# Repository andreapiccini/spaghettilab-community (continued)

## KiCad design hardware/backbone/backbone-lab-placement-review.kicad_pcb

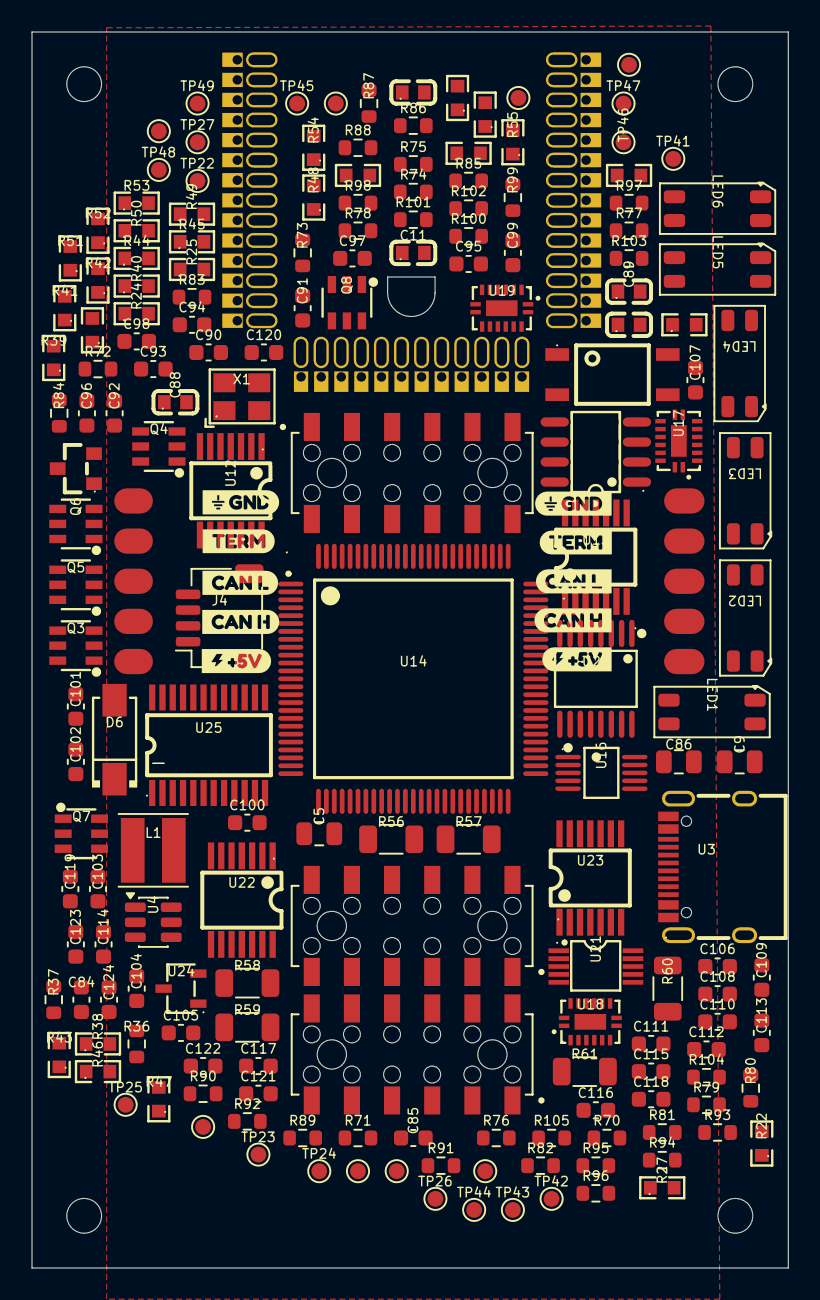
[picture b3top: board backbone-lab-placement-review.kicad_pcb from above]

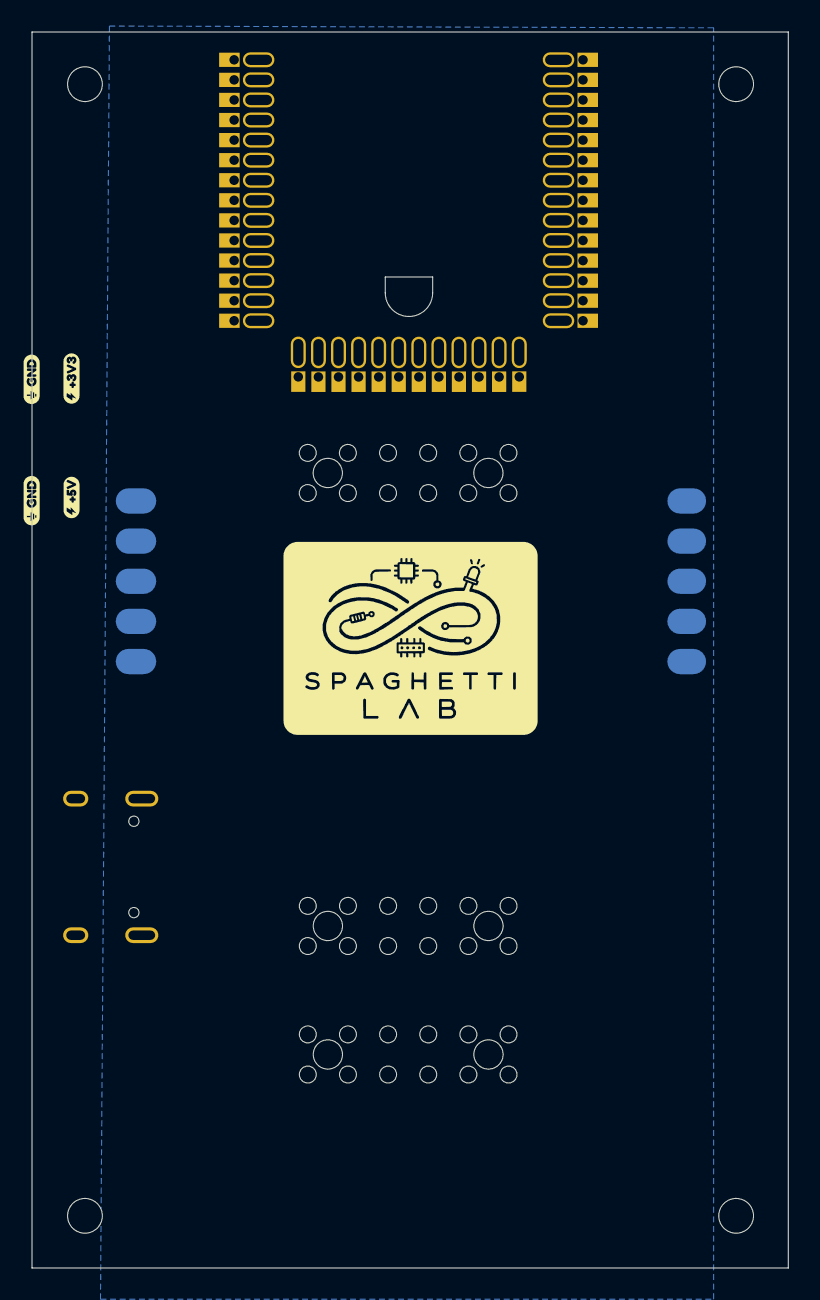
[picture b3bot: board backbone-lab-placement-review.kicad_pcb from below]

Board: 4 copper layers, 47.9 x 78.2 mm, 207 parts (13 on the bottom side), 125 nets, no tracks yet.

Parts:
C1, C74, C88, C89: 100nF; C0603
C5, C9, C86: 22uF; C_0805_2012Metric
C11: 1uF; C0603
C84, C85: 100nF/50V; C_0603_1608Metric
C90, C91, C92, C93, C94, C95, C96, C97, C98, C100, C101, C102, C105, C106, C114, C115, C116, C119, C120, C121, C122, C123, C124: 100nF; C_0603_1608Metric
C99, C103, C104, C107, C117, C118: 1uF; C_0603_1608Metric
C108, C109, C110, C111, C112, C113: 1nF; C_0603_1608Metric
D6: SS54_C22452; SMA_L4.4-W2.8-LS5.4-R-RD
H1, H2, H3, H4: MountingHole; MountingHole_2.2mm_M2_DIN965
J1, J3, J140: M20-7810645R; HARWIN_M20-7810645R
J2: FROM_PREVIOUS; Magnetic_J2_Edge_DualFace
J4: SM04B-SRSS-TB(LF)(SN); JST_SH_SM04B-SRSS-TB_1x04-1MP_P1.00mm_Horizontal
J9: TO NEXT; Magnetic_J9_Edge_DualFace
L1: 3.3uH; L_XRTC404012S
LED1, LED2, LED3, LED4, LED5, LED6: SK6812MINI-E; LED_SK6812MINI-E_FR4_Window_HandFormed
Q2: AO3401A; SOT-23_L2.9-W1.3-P1.90-LS2.4-BR
Q3, Q4, Q5, Q6, Q7, Q8: AO6604; SOT-23-6_L2.9-W1.6-P0.95-LS2.8-BL
R4: 470k; R0603
R5: 1k; R0603
R8: 120R; R0603
R15, R16: 10k; R0603
R17, R18: 33R DNP / ESP USB; R0603
R22, R27: 5.1k; R0603
R24, R25: 4.7k; R0603
R36: 33k 1%; R_0603_1608Metric
R37: 10k 1%; R_0603_1608Metric
R38, R39, R40, R41, R42, R43, R44, R45, R46, R47, R48, R49, R50, R51, R52, R53, R54, R55: 100k; R0603
R56, R57, R58, R59, R60, R61: 0.1R; R_1206_3216Metric
R70, R71, R74, R75, R76, R78, R103, R104, R105: 100k; R_0603_1608Metric
R72, R73, R83, R84: 10k; R_0603_1608Metric
R77: 4.7k 0.1% 25ppm; R_0603_1608Metric
R79, R80: 4.7k; R_0603_1608Metric
R81, R82: 22R; R_0603_1608Metric
R85, R86, R87, R88, R97: 1k; R_0603_1608Metric
R89, R90, R91, R92, R93, R94: 33R; R_0603_1608Metric
R95: 3.16k 0.1%; R_0603_1608Metric
R96: 10k 0.1%; R_0603_1608Metric
R98, R99, R100, R101, R102: 0R / ESP-only; R_0603_1608Metric
TP8, TP9, TP12, TP13, TP15, TP18, TP19, TP21: SMD/0.6mm; TestPoint_Pad_D1.0mm
TP22: AG_NRST; TestPoint_Pad_D1.0mm
TP23: AG_JTMS; TestPoint_Pad_D1.0mm
TP24: AG_JTCK; TestPoint_Pad_D1.0mm
TP25: AG_JTDI; TestPoint_Pad_D1.0mm
TP26: AG_JTDO; TestPoint_Pad_D1.0mm
TP27: AG_JNTRST; TestPoint_Pad_D1.0mm
TP41: DAC1; TestPoint_Pad_D1.0mm
TP42: ADC_SPARE_17; TestPoint_Pad_D1.0mm
TP43: ADC_SPARE_33; TestPoint_Pad_D1.0mm
TP44: ADC_SPARE_34; TestPoint_Pad_D1.0mm
TP45: ADC_SPARE_35; TestPoint_Pad_D1.0mm
TP46: ADC_SPARE_36; TestPoint_Pad_D1.0mm
TP47: AG_UART_RX; TestPoint_Pad_D1.0mm
TP48: AG_UART_TX; TestPoint_Pad_D1.0mm
TP49: AG_BOOT0; TestPoint_Pad_D1.0mm
U1: ESP32-S3-WROOM-1_1U_FlexyPin_Socket
U2: SN65HVD230DR; SOIC-8_L4.9-W3.9-P1.27-LS6.0-BL
U3: HC-TYPE-C-16P-01A; USB-C-SMD_HC-TYPE-C-16P-01A
U4: TPS562201DDCR; TSOT-23-6_Power
U8: G3VM-61VY3; SMD-4_L4.6-W3.7-P2.54-LS7.0-TL
U12, U13: SN74CBTLV3125PWR; TSSOP-14_L5.0-W4.4-P0.65-LS6.4-BL
U14: AG32VF407VGT6; LQFP-100_L14.0-W14.0-P0.50-LS16.0-TL
U16: INA226AIDGSR; MSOP-10_L3.0-W3.0-P0.50-LS5.0-BL
U17, U18, U19: 74HC4051BQ,115; DHVQFN-16_L3.5-W2.5-P0.50-BL-EP
U20: ADC128S102CIMTX/NOPB; TSSOP-16_L5.0-W4.4-P0.65-LS6.4-BL
U21: DAC60501ZDGSR; VSSOP-10_L3.0-W3.0-P0.50-LS4.9-BL
U22, U23: TLV9064IPWR; TSSOP-14_L5.0-W4.4-P0.65-LS6.4-BL
U24: REF3033AIDBZR; SOT-23-3_L3.0-W1.7-P0.95-LS2.9-BR
U25: TCA9535PWR(UMW); TSSOP-24_L7.8-W4.4-P0.65-LS6.4-BL
X1: 20MHz; OSC-SMD_4P-L3.2-W2.5-BL
kobee-studio-6AA93AD3, kobee-studio-6AA93ADA, kobee-studio-6AA93AE3, kobee-studio-6AA93AEC, kobee-studio-6AA93AF1, kobee-studio-6AA93AF7, kobee-studio-6AA93AFD, kobee-studio-6AA93B02, kobee-studio-6AAFA9BC, kobee-studio-6AAFA984, kobee-studio-6ACCF2B8, kobee-studio-6ACCF2C6, kobee-studio-6ACCF2D1, kobee-studio-6ACCF2D6, kobee-studio-6ACCF2E9, kobee-studio-6ACCF2F3, kobee-studio-6ACCF2F9, kobee-studio-6ACCF2FE, kobee-studio-6ACCF30E, kobee-studio-6ACCF303, kobee-studio-6ACCF308, kobee-studio-6ACCF312: Kobee Studio; kobee-studio-6AA82ECF

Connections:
5V: C5.1, C85.1, C102.1, C103.1, C114.1, C115.1, C116.1, C117.1, D6.2 (K), J2.1, J2.4, J9.1, Q2.2 (S), U4.3 (VIN), U4.5 (EN), U21.1, U22.4, U23.4, U24.1
/AG_BOOT0: R83.2, R87.2, TP49.1, U14.94 (BOOT0)
/AG_BOOT1: R84.2, U14.37 (BOOT1)
/AG_JNTRST_N: R73.2, TP27.1 (1_1), U14.90 (JNTRST_N)
/AG_JTCK: TP24.1 (1_1), U14.76 (JTCK)
/AG_JTDI: TP25.1 (1_1), U14.77 (JTDI)
/AG_JTDO: TP26.1 (1_1), U14.89 (JTDO)
/AG_JTMS: TP23.1 (1_1), U14.72 (JTMS)
/AG_NRST_N: C92.1, R72.2, R88.2, TP22.1 (1_1), U14.14 (NRST_N)
/AG_USB_DM: R81.1, U14.70 (USB_DM)
/AG_USB_DP: R82.1, U14.71 (USB_DP)
/BOOT: R15.2, TP9.1 (1_1), U1.27 (IO0)
/BUCK_BOOT: C84.1, U4.6 (VBST)
/BUCK_FB: R36.2, R37.1, U4.4 (VFB)
/BUCK_SW: C84.2, L1.1, U4.2 (SW)
/CLK20M: U14.12 (OSC_IN), U14.18 (CLK20M_FPGA), X1.3 (OUT)
/DAC_MONITOR: R97.2, TP41.1 (1_1), U20.10
/DAC_PRECISION: U21.2, U23.10
/DAC_REF_2V5: C118.1, U21.10
/DAC_S0: U14.78 (DAC_S0), U14.79 (DAC_S1), U19.10 (S1), U19.11 (S0)
/ESP_AG_BOOT0: R87.1, U1.8 (IO15)
/ESP_AG_RESET_N: R88.1, U1.9 (IO16)
/ESP_PROG_RX: R86.2, U1.25 (IO48)
/ESP_PROG_TX: R85.1, R102.1, U1.24 (IO47)
/INA_ALERT_N: R76.2, U14.84 (INA_ALERT_N), U16.3 (Alert)
/INA_SCL: R80.2, U14.83 (INA_SCL), U16.5 (SCL)
/INA_SDA: R79.2, U14.82 (INA_SDA), U16.4 (SDA)
/LAB_ADC_CS_N: R103.2, U14.15 (ADC_RAW/IN10), U20.1
/LAB_DAC_CS_N: R104.2, U14.16 (ADC_LIMIT/IN11), U21.7
/LAB_MISO: TP44.1 (1_1), U14.34 (ADC_IN15_SPARE), U20.15
/LAB_MOSI: TP43.1 (1_1), U14.33 (ADC_IN14_SPARE), U20.14, U21.8
/LAB_SCLK: R105.1, TP42.1 (1_1), U14.17 (ADC_IN12_SPARE), U20.16, U21.6
/LED_CHAIN_1: LED1.4 (DOUT), LED2.2 (DIN)
/LED_CHAIN_2: LED2.4 (DOUT), LED3.2 (DIN)
/LED_CHAIN_3: LED3.4 (DOUT), LED4.2 (DIN)
/LED_CHAIN_4: LED4.4 (DOUT), LED5.2 (DIN)
/LED_CHAIN_5: LED5.4 (DOUT), LED6.2 (DIN)
/MEAS_INHIBIT: R70.2, U14.5 (MEAS_INHIBIT), U17.6 (E_INHIBIT), U18.6 (E_INHIBIT)
/MEAS_S0: U14.2 (MEAS_S0), U17.11 (S0), U18.11 (S0)
/MEAS_S1: U14.3 (MEAS_S1), U17.10 (S1), U18.10 (S1)
/MEAS_S2: U14.4 (MEAS_S2), U17.9 (S2), U18.9 (S2)
/SHUNT_HIGH_SELECTED: U16.10 (VIN+), U17.3 (Z)
/SHUNT_LOW_SELECTED: U16.9 (VIN-), U18.3 (Z)
/USB_CC1: R22.1, U3.A5 (CC1)
/USB_CC2: R27.2, U3.B5 (CC2)
/VBUF_A0: C108.1, R89.2, U20.4
/VBUF_A1: C109.1, R90.2, U20.5
/VBUF_A2: C110.1, R91.2, U20.6
/VBUF_A3: C111.1, R92.2, U20.7
/VBUF_A4: C112.1, R93.2, U20.8
/VBUF_A5: C113.1, R94.2, U20.9
A0: J3.3, U1.7 (IO7), U12.2 (A), U14.38 (ESP_A0)
A1: J3.4, U1.12 (IO8), U12.5 (A), U14.39 (ESP_A1)
A2: J3.7, U1.17 (IO9), U12.9 (A), U14.40 (ESP_A2)
A3: J3.8, U1.18 (IO10), U12.12 (A), U14.41 (ESP_A3)
A4: J3.11, U1.39 (IO1), U13.2 (A), U14.42 (ESP_A4)
A5: J3.12, U1.38 (IO2), U13.5 (A), U14.43 (ESP_A5)
AG_BOOT_UART_RX: R85.2, TP47.1, U14.69 (ISO5_N)
AG_BOOT_UART_TX: R86.1, TP48.1, U14.68 (ISO4_N)
ALED: LED1.2 (DIN), R102.2, U14.7 (LED_DATA)
CAN_H: J2.2, J9.2, R8.1, U2.7 (CANH)
CAN_L: J2.3, J9.3, U2.6 (CANL), U8.4
CAN_RX: R101.2, U2.4 (R), U14.93 (CAN_RX)
CAN_TX: R100.2, U2.1 (D), U14.92 (CAN_TX)
CTRL13: R74.2, R98.1, U1.21 (IO13), U14.86 (SPI_CS_N)
CTRL14: R99.1, U1.22 (IO14), U14.87 (SPI_SCLK)
DAC_BYPASS_N: R78.2, U13.10 (~OE), U14.85 (DAC_BYPASS_N)
DAC_LIMITED: R77.2, U13.8 (B), U19.3 (Z)
DAC_RAW: R77.1, R95.1, R97.1, U13.9 (A), U23.8
GND: C1.2, C5.2, C9.2, C11.1, C74.1, C85.2, C86.2, C88.2, C89.2, C90.2, C91.2, C92.2, C93.2, C94.2, C95.2, C96.2, C97.2, C98.2, C99.2, C100.2, C101.2, C102.2, C103.2, C104.2, C105.2, C106.2, C107.2, C108.2, C109.2, C110.2, C111.2, C112.2, C113.2, C114.2, C115.2, C116.2, C117.2, C118.2, C119.2, C120.2, C121.2, C122.2, C123.2, C124.2, J2.5, J3.2, J3.6, J3.10, J4.1 (GND), J9.5, LED1.1 (GND), LED2.1 (GND), LED3.1 (GND), LED4.1 (GND), LED5.1 (GND), LED6.1 (GND), Q3.5 (S), Q4.5 (S), Q5.5 (S), Q6.5 (S), Q7.5 (S), Q8.5 (S), R4.1, R22.2, R27.1, R37.2, R39.2, R41.2, R43.2, R45.2, R47.2, R49.2, R71.2, R83.1, R84.1, R96.2, R105.2, TP12.1 (1_1), TP13.1 (1_1), TP21.1 (1_1), U1.1 (GND), U1.40 (GND), U2.2 (GND), U2.8 (RS), U3.1 (SHELL), U3.2 (SHELL), U3.3 (SHELL), U3.4 (SHELL), U3.A1B12 (GND), U3.B1A12 (GND), U4.1 (GND), U8.2, U12.7 (GND), U13.7 (GND), U14.10 (VSS33), U14.20 (VSSA), U14.27 (VSS33), U14.74 (VSS33), U14.80 (DAC_S2), U14.81 (DAC_INHIBIT), U14.99 (VSS33), U16.1 (A1), U16.2 (A0), U16.7 (GND), U16.8 (VBUS), U17.7 (VEE), U17.8 (GND), U18.7 (VEE), U18.8 (GND), U19.6 (E_INHIBIT), U19.7 (VEE), U19.8 (GND), U19.9 (S2), U20.3, U20.11, U20.12, U21.4, U21.5, U22.11, U23.11, U23.12, U24.3, U25.2, U25.3, U25.12, U25.21, X1.2 (GND)
IO3: R75.2, U1.15 (IO3), U14.97 (ESP_IRQ_N)
IO4: J4.3 (SDA), R24.2, U1.4 (IO4), U14.95 (EXT_I2C_SDA), U25.23
IO5: J4.4 (SCL), R25.2, U1.5 (IO5), U14.96 (EXT_I2C_SCL), U25.22
ISO_A0_N: R50.2, U12.1 (~OE), U14.64 (ISO0_N), U25.17
ISO_A1_N: R51.2, U12.4 (~OE), U14.65 (ISO1_N), U25.18
ISO_A2_N: R52.2, U12.10 (~OE), U14.66 (ISO2_N), U25.19
ISO_A3_N: R53.2, U12.13 (~OE), U14.67 (ISO3_N), U25.20
ISO_A4_N: R54.2, R98.2, TP45.1 (1_1), U13.1 (~OE), U14.35 (ADC_IN8_SPARE)
ISO_A5_N: R55.2, R99.2, TP46.1 (1_1), U13.4 (~OE), U14.36 (ADC_IN9_SPARE)
LAB_3V3: C104.1, C105.1, C106.1, C107.1, C120.1, U20.2, U20.13, U24.2
N_A0: Q3.4 (D), Q3.6 (D), R56.1, U12.3 (B), U14.44 (DRIVE_A0), U17.13 (Y0), U19.13 (Y0)
N_A1: Q4.4 (D), Q4.6 (D), R57.1, U12.6 (B), U14.45 (DRIVE_A1), U17.14 (Y1), U19.14 (Y1)
N_A2: Q5.4 (D), Q5.6 (D), R58.1, U12.8 (B), U14.46 (DRIVE_A2), U17.15 (Y2), U19.15 (Y2)
N_A3: Q6.4 (D), Q6.6 (D), R59.1, U12.11 (B), U14.47 (DRIVE_A3), U17.12 (Y3), U19.12 (Y3)
N_A4: Q7.4 (D), Q7.6 (D), R60.1, U13.3 (B), U14.48 (DRIVE_A4), U17.1 (Y4), U19.1 (Y4)
N_A5: Q8.4 (D), Q8.6 (D), R61.1, U13.6 (B), U14.51 (DRIVE_A5), U17.5 (Y5), U19.5 (Y5)
N_GATE_0: Q3.1 (G), R39.1, U14.53 (N_GATE0), U25.5
N_GATE_1: Q4.1 (G), R41.1, U14.55 (N_GATE1), U25.7
N_GATE_2: Q5.1 (G), R43.1, U14.57 (N_GATE2), U25.9
N_GATE_3: Q6.1 (G), R45.1, U14.59 (N_GATE3), U25.11
N_GATE_4: Q7.1 (G), R47.1, U14.61 (N_GATE4), U25.14
N_GATE_5: Q8.1 (G), R49.1, U14.63 (N_GATE5), U25.16
unnamed: Q2.3 (D), R5.2
unnamed: R5.1, U8.1
unnamed: R8.2, U8.3
unnamed: R17.2, U1.14 (USB_D+)
unnamed: R18.2, U1.13 (USB_D-)
unnamed: R89.1, U22.1, U22.2
unnamed: R90.1, U22.6, U22.7
unnamed: R91.1, U22.8, U22.9
unnamed: R92.1, U22.13, U22.14
unnamed: R93.1, U23.1, U23.2
unnamed: R94.1, U23.6, U23.7
unnamed: R95.2, R96.1, U23.9
unnamed: U23.13, U23.14
PORT_A0: J1.1, J1.2, J140.1, J140.2, R56.2, U14.23 (ADC_A0/IN0), U18.13 (Y0), U22.3
PORT_A1: J1.3, J1.4, J140.3, J140.4, R57.2, U14.24 (ADC_A1/IN1), U18.14 (Y1), U22.5
PORT_A2: J1.5, J1.6, J140.5, J140.6, R58.2, U14.25 (ADC_A2/IN2), U18.15 (Y2), U22.10
PORT_A3: J1.7, J1.8, J140.7, J140.8, R59.2, U14.26 (ADC_A3/IN3), U18.12 (Y3), U22.12
PORT_A4: J1.9, J1.10, J140.9, J140.10, R60.2, U14.31 (ADC_A4/IN6), U18.1 (Y4), U23.3
PORT_A5: J1.11, J1.12, J140.11, J140.12, R61.2, U14.32 (ADC_A5/IN7), U18.5 (Y5), U23.5
P_GATE_0: Q3.3 (G), R38.2, U14.52 (P_GATE0_N), U25.4
P_GATE_1: Q4.3 (G), R40.2, U14.54 (P_GATE1_N), U25.6
P_GATE_2: Q5.3 (G), R42.2, U14.56 (P_GATE2_N), U25.8
P_GATE_3: Q6.3 (G), R44.2, U14.58 (P_GATE3_N), U25.10
P_GATE_4: Q7.3 (G), R46.2, U14.60 (P_GATE4_N), U25.13
P_GATE_5: Q8.3 (G), R48.2, U14.62 (P_GATE5_N), U25.15
SPI_MISO: R101.1, TP18.1 (1_1), U1.36 (RXD0), U14.91 (SPI_MISO)
SPI_MOSI: R100.1, TP19.1 (1_1), U1.37 (TXD0), U14.88 (SPI_MOSI)
TERM_CTRL_OUT: J9.4, Q2.1 (G), R4.2
USB_D+: R17.1, R82.2, U3.A6 (D+), U3.B6 (D+)
USB_D-: R18.1, R81.2, U3.A7 (D-), U3.B7 (D-)
VBUS: D6.1 (A), U3.A4B9 (VBUS), U3.B4A9 (VBUS)
VCORE: C1.1, C9.1, C74.2, C86.1, C88.1, C89.1, C90.1, C91.1, C93.1, C94.1, C95.1, C96.1, C97.1, C98.1, C99.1, C100.1, C101.1, C119.1, C121.1, C122.1, C123.1, C124.1, J3.1, J3.5, J3.9, J4.2 (+3V3), L1.2, LED1.3 (VDD), LED2.3 (VDD), LED3.3 (VDD), LED4.3 (VDD), LED5.3 (VDD), LED6.3 (VDD), Q3.2 (S), Q4.2 (S), Q5.2 (S), Q6.2 (S), Q7.2 (S), Q8.2 (S), R15.1, R16.1, R24.1, R25.1, R36.1, R38.1, R40.1, R42.1, R44.1, R46.1, R48.1, R50.1, R51.1, R52.1, R53.1, R54.1, R55.1, R70.1, R71.1, R72.1, R73.1, R74.1, R75.1, R76.1, R78.1, R79.1, R80.1, R103.1, R104.1, TP15.1 (1_1), U1.2 (3V3), U2.3 (VCC), U12.14 (VCC), U13.13 (~OE), U13.14 (VCC), U14.6 (VBAT), U14.11 (VDD33), U14.21 (VREFP), U14.22 (VDDA), U14.28 (VDD33), U14.50 (VDD33), U14.75 (VDD33), U14.100 (VDD33), U16.6 (VS+), U17.16 (VCC), U17.17 (EP_VCC), U18.16 (VCC), U18.17 (EP_VCC), U19.16 (VCC), U19.17 (EP_VCC), U25.24, X1.1 (OE/#ST), X1.4 (VCC)
~RESET: C11.2, R16.2, TP8.1 (1_1), U1.3 (EN), U14.98 (ESP_RESET_OD)

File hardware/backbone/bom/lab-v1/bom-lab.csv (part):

Reference,Value,Footprint,LCSC,ESP_optional
C1,100nF,SpaghettiLAB:C0603,C1591,no
C5,22uF,Capacitor_SMD:C_0805_2012Metric,C45783,no
C9,22uF,Capacitor_SMD:C_0805_2012Metric,C45783,no
C11,1uF,SpaghettiLAB:C0603,C128624,no
C74,100nF,SpaghettiLAB:C0603,C1591,no
C84,100nF/50V,Capacitor_SMD:C_0603_1608Metric,C14663,no
C85,100nF/50V,Capacitor_SMD:C_0603_1608Metric,C14663,no
C86,22uF,Capacitor_SMD:C_0805_2012Metric,C45783,no
C88,100nF,SpaghettiLAB:C0603,C14663,no
C89,100nF,SpaghettiLAB:C0603,C14663,no
C90,100nF,Capacitor_SMD:C_0603_1608Metric,C14663,no
C91,100nF,Capacitor_SMD:C_0603_1608Metric,C14663,no
C92,100nF,Capacitor_SMD:C_0603_1608Metric,C14663,no
C93,100nF,Capacitor_SMD:C_0603_1608Metric,C14663,no
C94,100nF,Capacitor_SMD:C_0603_1608Metric,C14663,no
C95,100nF,Capacitor_SMD:C_0603_1608Metric,C14663,no
C96,100nF,Capacitor_SMD:C_0603_1608Metric,C14663,no
C97,100nF,Capacitor_SMD:C_0603_1608Metric,C14663,no
C98,100nF,Capacitor_SMD:C_0603_1608Metric,C14663,no
C99,1uF,Capacitor_SMD:C_0603_1608Metric,C15849,no
C100,100nF,Capacitor_SMD:C_0603_1608Metric,C14663,no
C101,100nF,Capacitor_SMD:C_0603_1608Metric,C14663,no
C121,100nF,Capacitor_SMD:C_0603_1608Metric,C14663,no
C122,100nF,Capacitor_SMD:C_0603_1608Metric,C14663,no
C123,100nF,Capacitor_SMD:C_0603_1608Metric,C14663,no
C124,100nF,Capacitor_SMD:C_0603_1608Metric,C14663,no
D6,SS54_C22452,SpaghettiLAB:SMA_L4.4-W2.8-LS5.4-R-RD,C22452,no
H1,MountingHole,MountingHole:MountingHole_2.2mm_M2_DIN965,,no
H2,MountingHole,MountingHole:MountingHole_2.2mm_M2_DIN965,,no
H3,MountingHole,MountingHole:MountingHole_2.2mm_M2_DIN965,,no
H4,MountingHole,MountingHole:MountingHole_2.2mm_M2_DIN965,,no
J1,M20-7810645R,SpaghettiLAB:HARWIN_M20-7810645R,C6585798,no
J2,FROM_PREVIOUS,SpaghettiLAB:Magnetic_J2_Edge_DualFace,C41361292,no
J3,M20-7810645R,SpaghettiLAB:HARWIN_M20-7810645R,C6585798,no
J4,SM04B-SRSS-TB(LF)(SN),SpaghettiLAB:JST_SH_SM04B-SRSS-TB_1x04-1MP_P1.00mm_Horizontal,C160404,no
J5,FH12-24S-0.5SH(55),SpaghettiLAB:Hirose_FH12-24S-0.5SH_1x24-1MP_P0.50mm_Horizontal,C202112,no
J9,TO NEXT,SpaghettiLAB:Magnetic_J9_Edge_DualFace,C41361293,no
J140,M20-7810645R,SpaghettiLAB:HARWIN_M20-7810645R,C6585798,no
L1,3.3uH,SpaghettiLAB:L_XRTC404012S,C39846848,no
LED1,SK6812MINI-E,SpaghettiLAB:LED_SK6812MINI-E_FR4_Window_HandFormed,C5149201,no
LED2,SK6812MINI-E,SpaghettiLAB:LED_SK6812MINI-E_FR4_Window_HandFormed,C5149201,no
LED3,SK6812MINI-E,SpaghettiLAB:LED_SK6812MINI-E_FR4_Window_HandFormed,C5149201,no
LED4,SK6812MINI-E,SpaghettiLAB:LED_SK6812MINI-E_FR4_Window_HandFormed,C5149201,no
LED5,SK6812MINI-E,SpaghettiLAB:LED_SK6812MINI-E_FR4_Window_HandFormed,C5149201,no
LED6,SK6812MINI-E,SpaghettiLAB:LED_SK6812MINI-E_FR4_Window_HandFormed,C5149201,no
NT1,NetTie_2,,,no
Q2,AO3401A,SpaghettiLAB:SOT-23_L2.9-W1.3-P1.90-LS2.4-BR,C15127,no
Q3,AO6604,LCSC_Ports:SOT-23-6_L2.9-W1.6-P0.95-LS2.8-BL,C5182068,no
Q4,AO6604,LCSC_Ports:SOT-23-6_L2.9-W1.6-P0.95-LS2.8-BL,C5182068,no
Q5,AO6604,LCSC_Ports:SOT-23-6_L2.9-W1.6-P0.95-LS2.8-BL,C5182068,no
Q6,AO6604,LCSC_Ports:SOT-23-6_L2.9-W1.6-P0.95-LS2.8-BL,C5182068,no
Q7,AO6604,LCSC_Ports:SOT-23-6_L2.9-W1.6-P0.95-LS2.8-BL,C5182068,no
Q8,AO6604,LCSC_Ports:SOT-23-6_L2.9-W1.6-P0.95-LS2.8-BL,C5182068,no
R4,470k,SpaghettiLAB:R0603,C114622,no
R5,1k,SpaghettiLAB:R0603,C2907002,no
R8,120R,SpaghettiLAB:R0603,C2906988,no
R15,10k,SpaghettiLAB:R0603,C25804,no
R16,10k,SpaghettiLAB:R0603,C25804,no
R17,33R / ESP USB,SpaghettiLAB:R0603,C2909394,no
R18,33R / ESP USB,SpaghettiLAB:R0603,C2909394,no
R22,5.1k,SpaghettiLAB:R0603,C2907044,no
R24,4.7k,SpaghettiLAB:R0603,C23162,no
R25,4.7k,SpaghettiLAB:R0603,C23162,no
R27,5.1k,SpaghettiLAB:R0603,C2907044,no
R36,33k 1%,Resistor_SMD:R_0603_1608Metric,C4216,no
R37,10k 1%,Resistor_SMD:R_0603_1608Metric,C25804,no
R38,100k,SpaghettiLAB:R0603,C25803,no
R39,100k,SpaghettiLAB:R0603,C25803,no
R40,100k,SpaghettiLAB:R0603,C25803,no
R41,100k,SpaghettiLAB:R0603,C25803,no
R42,100k,SpaghettiLAB:R0603,C25803,no
R43,100k,SpaghettiLAB:R0603,C25803,no
R44,100k,SpaghettiLAB:R0603,C25803,no
R45,100k,SpaghettiLAB:R0603,C25803,no
R46,100k,SpaghettiLAB:R0603,C25803,no
R47,100k,SpaghettiLAB:R0603,C25803,no
R48,100k,SpaghettiLAB:R0603,C25803,no
R49,100k,SpaghettiLAB:R0603,C25803,no
R50,100k,SpaghettiLAB:R0603,C25803,no
R51,100k,SpaghettiLAB:R0603,C25803,no
R52,100k,SpaghettiLAB:R0603,C25803,no
R53,100k,SpaghettiLAB:R0603,C25803,no
R54,100k,SpaghettiLAB:R0603,C25803,no
R55,100k,SpaghettiLAB:R0603,C25803,no
R56,0.1R,Resistor_SMD:R_1206_3216Metric,C5123673,no
R57,0.1R,Resistor_SMD:R_1206_3216Metric,C5123673,no
R58,0.1R,Resistor_SMD:R_1206_3216Metric,C5123673,no
R59,0.1R,Resistor_SMD:R_1206_3216Metric,C5123673,no
R60,0.1R,Resistor_SMD:R_1206_3216Metric,C5123673,no
R61,0.1R,Resistor_SMD:R_1206_3216Metric,C5123673,no
R70,10k,Resistor_SMD:R_0603_1608Metric,C25804,no
R71,100k,Resistor_SMD:R_0603_1608Metric,C25803,no
R72,10k,Resistor_SMD:R_0603_1608Metric,C25804,no
R73,10k,Resistor_SMD:R_0603_1608Metric,C25804,no
R74,100k,Resistor_SMD:R_0603_1608Metric,C25803,no
R75,100k,Resistor_SMD:R_0603_1608Metric,C25803,no
R76,100k,Resistor_SMD:R_0603_1608Metric,C25803,no
R77,4.7k 0.1% 25ppm,Resistor_SMD:R_0603_1608Metric,C513565,no
R78,100k,Resistor_SMD:R_0603_1608Metric,C25803,no
R79,10k,Resistor_SMD:R_0603_1608Metric,C25804,no
R80,10k,Resistor_SMD:R_0603_1608Metric,C25804,no
R83,10k,Resistor_SMD:R_0603_1608Metric,C25804,no
R84,10k,Resistor_SMD:R_0603_1608Metric,C25804,no
R85,1k,Resistor_SMD:R_0603_1608Metric,C21190,no
R86,1k,Resistor_SMD:R_0603_1608Metric,C21190,no
R87,1k,Resistor_SMD:R_0603_1608Metric,C21190,no
R88,1k,Resistor_SMD:R_0603_1608Metric,C21190,no
TP8,SMD/0.6mm,TestPoint:TestPoint_Pad_D1.0mm,,no
TP9,SMD/0.6mm,TestPoint:TestPoint_Pad_D1.0mm,,no
TP12,SMD/0.6mm,TestPoint:TestPoint_Pad_D1.0mm,,no
TP13,SMD/0.6mm,TestPoint:TestPoint_Pad_D1.0mm,,no
TP15,SMD/0.6mm,TestPoint:TestPoint_Pad_D1.0mm,,no
TP18,SMD/0.6mm,TestPoint:TestPoint_Pad_D1.0mm,,no
TP19,SMD/0.6mm,TestPoint:TestPoint_Pad_D1.0mm,,no
TP21,SMD/0.6mm,TestPoint:TestPoint_Pad_D1.0mm,,no
TP22,AG_NRST,TestPoint:TestPoint_Pad_D1.0mm,,no
TP23,AG_JTMS,TestPoint:TestPoint_Pad_D1.0mm,,no
TP24,AG_JTCK,TestPoint:TestPoint_Pad_D1.0mm,,no
TP25,AG_JTDI,TestPoint:TestPoint_Pad_D1.0mm,,no
TP26,AG_JTDO,TestPoint:TestPoint_Pad_D1.0mm,,no
TP27,AG_JNTRST,TestPoint:TestPoint_Pad_D1.0mm,,no
TP41,DAC1_SPARE,TestPoint:TestPoint_Pad_D1.0mm,,no
TP42,SPARE_IO_17,TestPoint:TestPoint_Pad_D1.0mm,,no
TP43,SPARE_IO_33,TestPoint:TestPoint_Pad_D1.0mm,,no
TP44,SPARE_IO_34,TestPoint:TestPoint_Pad_D1.0mm,,no
TP45,ISO4_CTRL,TestPoint:TestPoint_Pad_D1.0mm,,no
TP46,ISO5_CTRL,TestPoint:TestPoint_Pad_D1.0mm,,no
TP47,AG_UART_RX,TestPoint:TestPoint_Pad_D1.0mm,,no
TP48,AG_UART_TX,TestPoint:TestPoint_Pad_D1.0mm,,no
TP49,AG_BOOT0,TestPoint:TestPoint_Pad_D1.0mm,,no
U1,ESP32-S3-WROOM-1_1U_FlexyPin_Socket,FlexyPin:ESP32-S3-WROOM-1_1U_FlexyPin_Socket,C2913201,yes
U2,SN65HVD230DR,SpaghettiLAB:SOIC-8_L4.9-W3.9-P1.27-LS6.0-BL,C12084,no
U3,HC-TYPE-C-16P-01A,SpaghettiLAB:USB-C-SMD_HC-TYPE-C-16P-01A,C2894897,no
U4,TPS562201DDCR,SpaghettiLAB:TSOT-23-6_Power,C90061,no
U8,G3VM-61VY3,SpaghettiLAB:SMD-4_L4.6-W3.7-P2.54-LS7.0-TL,C2152318,no
U12,SN74CBTLV3125PWR,LCSC_Ports:TSSOP-14_L5.0-W4.4-P0.65-LS6.4-BL,C406866,no
U13,SN74CBTLV3125PWR,LCSC_Ports:TSSOP-14_L5.0-W4.4-P0.65-LS6.4-BL,C406866,no
U14,AG32VF407VGT6,LCSC_Ports:LQFP-100_L14.0-W14.0-P0.50-LS16.0-TL,C5336269,no
U16,INA226AIDGSR,LCSC_Ports:MSOP-10_L3.0-W3.0-P0.50-LS5.0-BL,C49851,no
U17,"74HC4051BQ,115",LCSC_Ports:DHVQFN-16_L3.5-W2.5-P0.50-BL-EP,C128429,no
U18,"74HC4051BQ,115",LCSC_Ports:DHVQFN-16_L3.5-W2.5-P0.50-BL-EP,C128429,no
U19,"74HC4051BQ,115",LCSC_Ports:DHVQFN-16_L3.5-W2.5-P0.50-BL-EP,C128429,no
X1,20MHz,LCSC_Ports:OSC-SMD_4P-L3.2-W2.5-BL,C390499,no
U25,TCA9535PWR(UMW),LCSC_Ports:TSSOP-24_L7.8-W4.4-P0.65-LS6.4-BL,C22396388,no
U26,SN74LVC1G3157DCKR,Package_TO_SOT_SMD:SOT-363_SC-70-6,C38663,no
U27,SN74LVC1G3157DCKR,Package_TO_SOT_SMD:SOT-363_SC-70-6,C38663,no
U28,SN74LVC1G3157DCKR,Package_TO_SOT_SMD:SOT-363_SC-70-6,C38663,no
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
